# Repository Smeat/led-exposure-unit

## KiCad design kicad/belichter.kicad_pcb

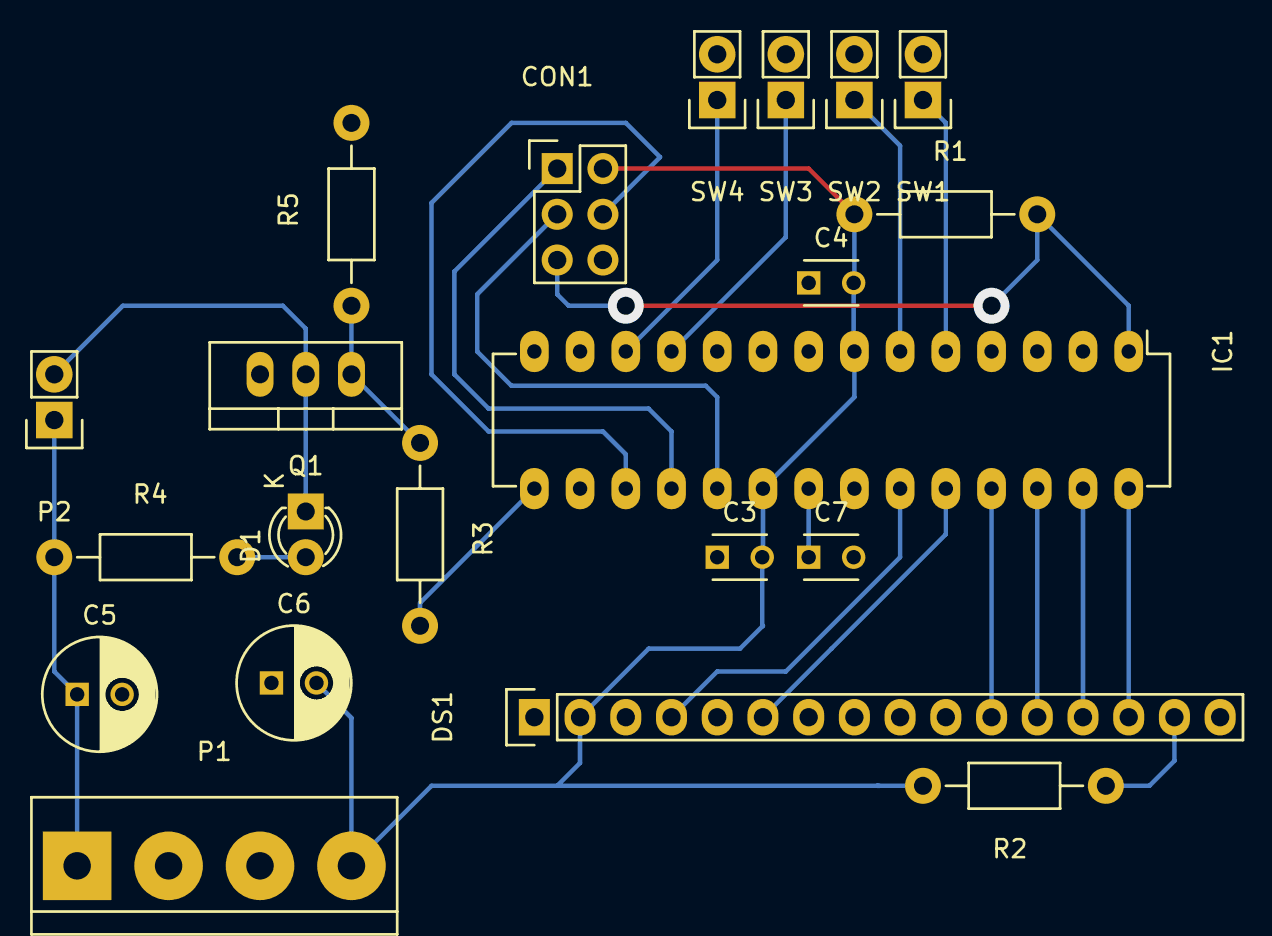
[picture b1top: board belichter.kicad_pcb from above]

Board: 2 copper layers, 21 parts (0 on the bottom side), 23 nets.

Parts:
C3, C4, C7: 100nF; C_Disc_D3_P2.5
C5, C6: 100nF; C_Radial_D6.3_L11.2_P2.5
CON1: AVR-ISP-6; Pin_Header_Straight_2x03
D1: LED; LED-3MM
DS1: LCD16X2; Pin_Header_Straight_1x16
IC1: ATMEGA8-P; DIP-28_W7.62mm_LongPads
P1: CONN_01X04; bornier4
P2: CONN_01X02; Pin_Header_Straight_1x02
Q1: Q_NMOS_GDS; TO-220_Neutral123_Vertical
R1: 100k; Resistor_Horizontal_RM10mm
R2: R; Resistor_Horizontal_RM10mm
R3: 1k; Resistor_Horizontal_RM10mm
R4: 1K; Resistor_Horizontal_RM10mm
R5: 10k; Resistor_Horizontal_RM10mm
SW1, SW2, SW3, SW4: SW_PUSH; Pin_Header_Straight_1x02

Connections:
+5V: C3.2, C4.2, C6.2, CON1.2, DS1.2, IC1.7, IC1.20, P1.4, R1.1, R2.2
+12V: C5.1, P1.1, P2.1, R4.1
GND: C3.1, C4.1, C5.2, C6.1, C7.2, CON1.6, DS1.1, DS1.3, DS1.5, DS1.16, IC1.8, IC1.22, P1.2, P1.3, Q1.3, R5.2, SW1.2, SW2.2, SW3.2, SW4.2
LCD_D4: DS1.11, IC1.25
LCD_D5: DS1.12, IC1.26
LCD_D6: DS1.13, IC1.27
LCD_D7: DS1.14, IC1.28
LCD_E: DS1.6, IC1.24
LCD_RS: DS1.4, IC1.23
LED_ON: IC1.15, R3.2
MISO: CON1.1, IC1.18
MOSI: CON1.4, IC1.17
unnamed: C7.1, IC1.21
unnamed: D1.1, P2.2, Q1.2
unnamed: D1.2, R4.2
unnamed: DS1.15, R2.1
unnamed: IC1.5, SW1.1
unnamed: IC1.6, SW2.1
unnamed: IC1.11, SW3.1
unnamed: IC1.12, SW4.1
unnamed: Q1.1, R3.1, R5.1
RST: CON1.5, IC1.1, R1.2
SCK: CON1.3, IC1.19

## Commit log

2015-08-08 Rename folder
2015-08-08 geda: Add jumper1 symbol.
2015-12-06 Update scad model and geda files.
2015-12-06 Switch to kicad.
